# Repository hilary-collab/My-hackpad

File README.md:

# Why not ?

Welcome to my custom Hackpad project. "Why not" is a 5 key macropad featuring a Rotary Encoder, an OLED screen, and 2 WS2812B Leds.

##  Features
- **Controller:** Seeed Studio XIAO RP2040
- **Layout:** 5 Physical Mechanical Switches + 1 Integrated Rotary Encoder Press 
- **Display:** 0.91" I2C OLED Screen 
- **RGB Lighting:** SK6812MINI-E Reverse-Mount LEDs
- **Enclosure:** Custom 3D-printable Top Layer designed in Onshape 
##  QMK Firmware 
This Hackpad used QMK Firmware- but certain changes might be make afterwards !
1. **Character Mode (SW1):** Pressing the first switch dynamically changes the OLED state to wake up an animated character.
2. **Timer Mode (SW2):** Features an onboard tracking stopwatch that can be toggled on/off.
3. **Smart Menu Navigation (SW3 & SW4):** Use these dedicated directional switches to navigate Left/Right or Up/Down through the main menu.
4. **Settings Menu (SW5):** Quickly jumps back to the Main Menu overlay.
5. **Interactive Double-Click Detection:** Double-clicking the **Rotary Encoder Press (SW6/D7)** inside the Time or Date screen unlocks the editing state, allowing you to turn the knob to dynamically adjust clock values and day constraints.

## PCB
Here is my pcb ! It is made in Kicad.
-schmetic

-routing

## Case
I have used Onshape for my case. It is a simple sanwich case with hole made for type c on the right.

## BOM
-Here are things you need to make "Why not?" !!!
BOM file is atached up there 
- **1x Unsoldered Seeed Studio XIAO RP2040**
- **5x MX-Style Mechanical Switches**
- **1x EC11 Rotary Encoder**
- **1x 0.91-inch OLED Display** 
- **2x SK6812 MINI-E LEDs** 
- **5x White Blank DSA Keycaps**
- **4x M3x16mm Screws**
- **4x M3x5mmx4mm Heatset Brass Inserts**

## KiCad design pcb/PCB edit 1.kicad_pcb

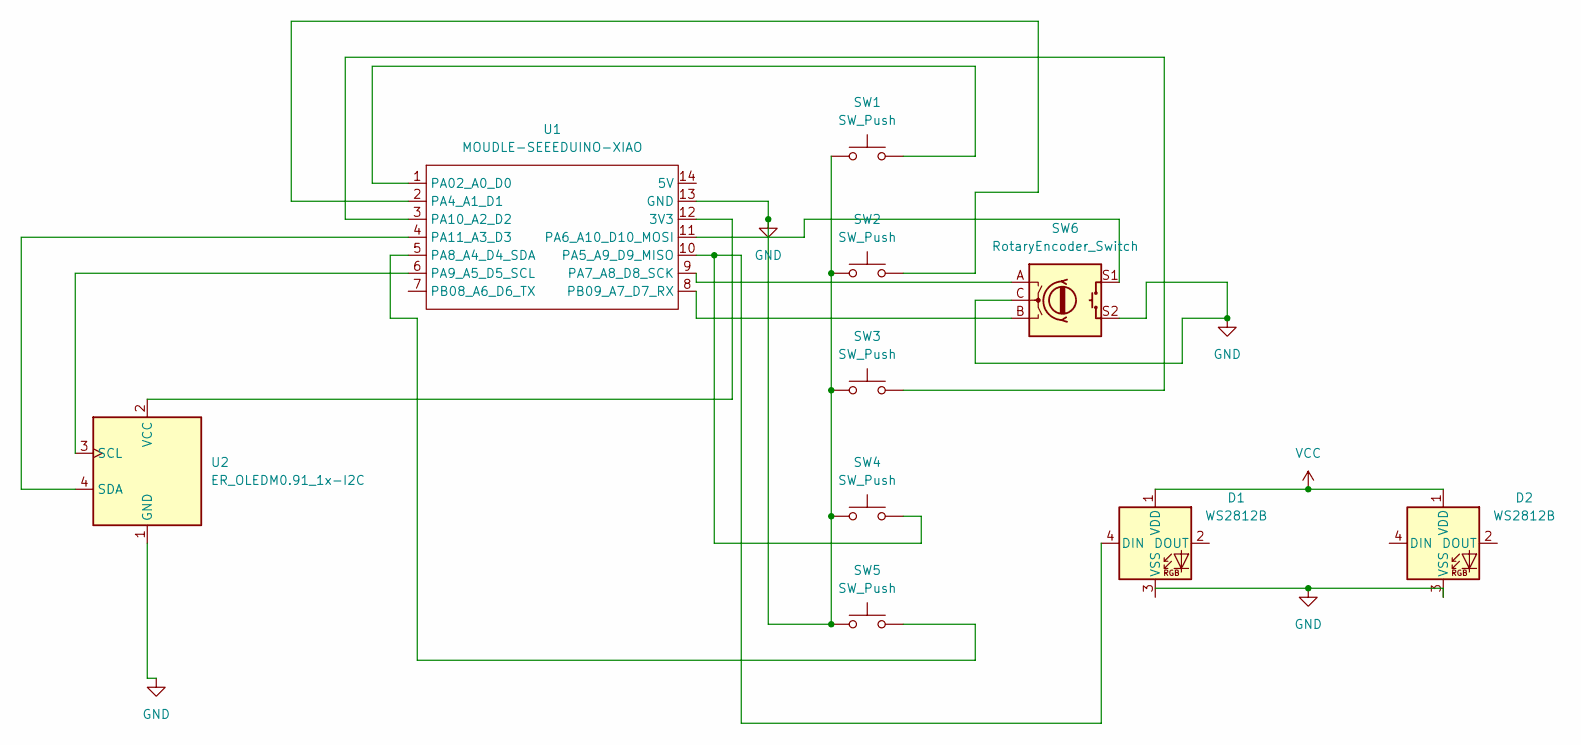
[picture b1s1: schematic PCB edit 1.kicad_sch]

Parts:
D1, D2: WS2812B; LED_SK6812MINI-E_3.2x2.8mm_P1.5mm_ReverseMount
SW1, SW2, SW3, SW4, SW5: SW_Push; SW_Cherry_MX_1.00u_PCB
SW6: RotaryEncoder_Switch; RotaryEncoder_Alps_EC11E-Switch_Vertical_H20mm_MountingHoles
U1: MOUDLE-SEEEDUINO-XIAO; XIAO-Generic-Hybrid-14P-2.54-21X17.8MM
U2: ER_OLEDM0.91_1x-I2C

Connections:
GND: D2.3 (VSS), SW1.1, SW2.1, SW3.1, SW4.1, SW5.1, SW6.C, SW6.S2, U1.13 (GND), U2.1 (GND)
unnamed: D1.4 (DIN), SW4.2, U1.10 (PA5_A9_D9_MISO)
unnamed: U1.12 (3V3), U2.2 (VCC)
unnamed: SW1.2, U1.1 (PA02_A0_D0)
unnamed: SW2.2, U1.2 (PA4_A1_D1)
unnamed: SW6.S1, U1.11 (PA6_A10_D10_MOSI)
unnamed: SW6.A, U1.9 (PA7_A8_D8_SCK)
unnamed: SW5.2, U1.5 (PA8_A4_D4_SDA)
unnamed: U1.6 (PA9_A5_D5_SCL), U2.3 (SCL)
unnamed: SW3.2, U1.3 (PA10_A2_D2)
unnamed: U1.4 (PA11_A3_D3), U2.4 (SDA)
unnamed: SW6.B, U1.8 (PB09_A7_D7_RX)
VCC: D1.1 (VDD), D2.1 (VDD)

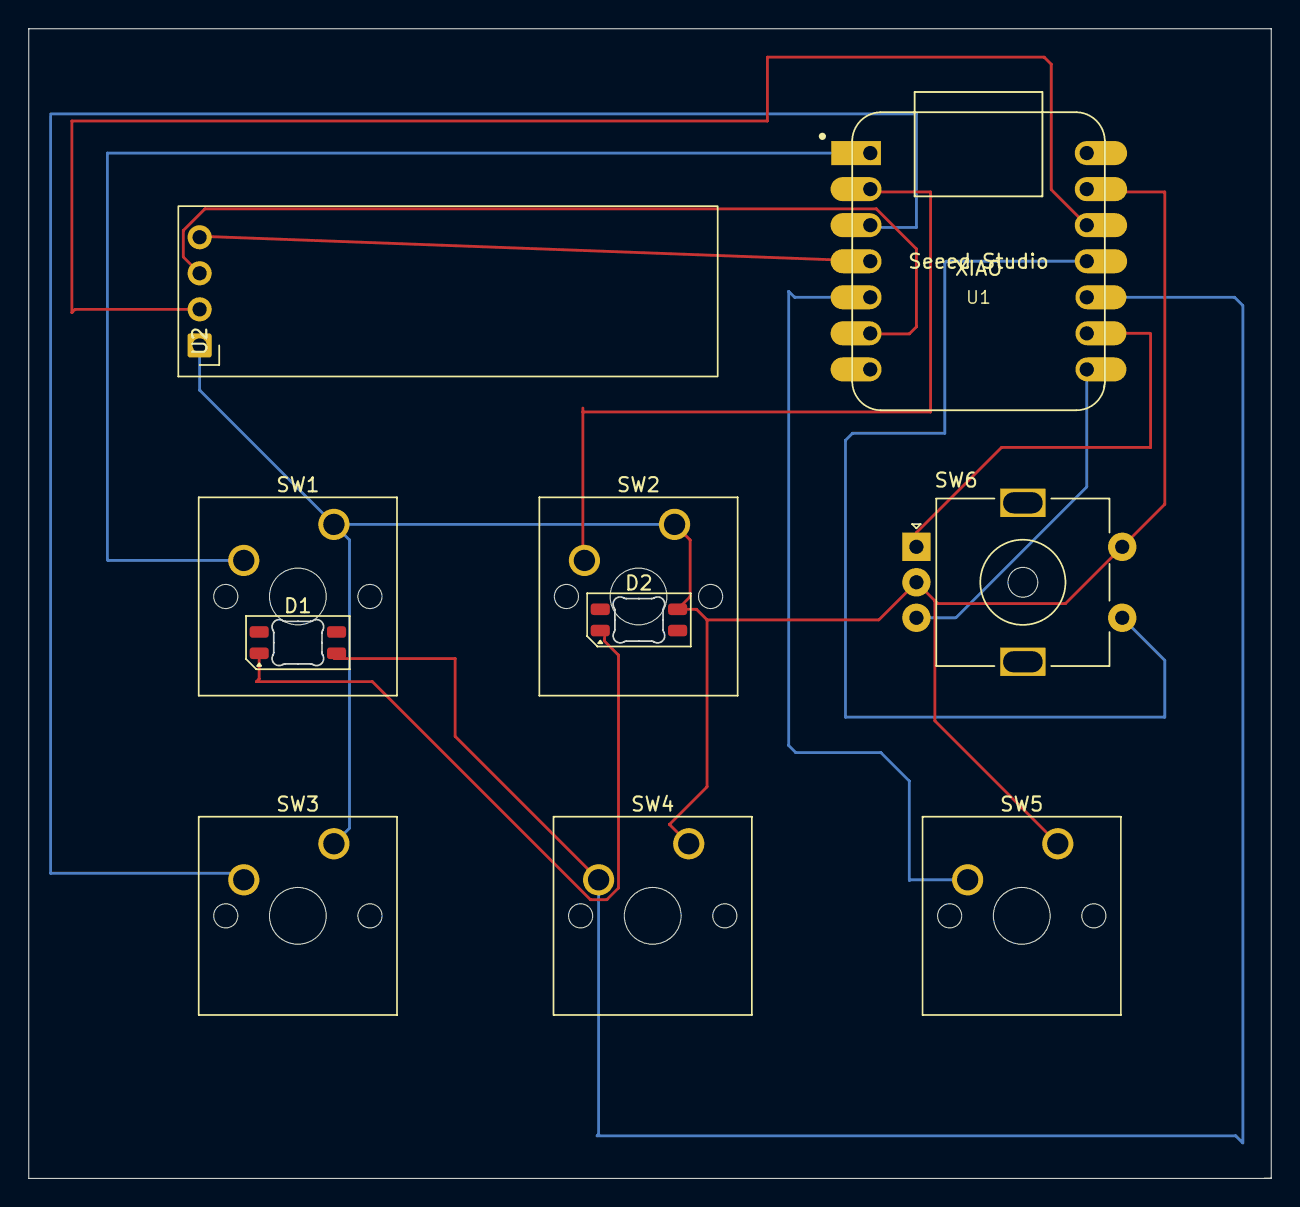
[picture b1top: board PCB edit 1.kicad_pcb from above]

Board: 2 copper layers, 87.5 x 81.0 mm, 10 parts (0 on the bottom side), 13 nets.
